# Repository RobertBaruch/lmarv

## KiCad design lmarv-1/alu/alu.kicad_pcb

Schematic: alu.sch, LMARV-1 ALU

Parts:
C1, C2, C3, C4, C5, C14, C15, C16, C24, C25, C26, C27, C28, C29, C30, C31, C32, C33, C34, C35, C36, C37, C38, C39, C40, C41, C42, C43, C44, C45, C46, C47, C48, C49, C50, C51, C52, C57, C58, C59: 100n; C_0603_1608Metric
C100, C101, C102: 1u; CP_Elec_4x4.5
D1, D2: APTD2012LSURCK; D_0805_Wide
P1: dual-pcie-cardedge_split; PCI-EXPRESS
R1, R2, R3, R4: 10k; R_0603_1608Metric
R5, R6: 3k3; R_0603_1608Metric
U1, U14, U16, U26, U27, U37, U40, U41, U42, U43, U44: 74LVC541; TSSOP-20_4.4x6.5mm_P0.65mm
U2: 74LVC04; TSSOP-14_4.4x5mm_P0.65mm
U3: 74LVC32; TSSOP-14_4.4x5mm_P0.65mm
U15: AT28BV64B-20JU; PLCC-32_THT-Socket
U24, U25, U38: 74LVC541_a; TSSOP-20_4.4x6.5mm_P0.65mm
U28, U29, U30, U31, U32, U33, U34, U39, U45, U46, U47, U48, U49, U50, U51, U52: IS61LV256AL; TSOP-I-28_18.4x8mm_Pitch0.55mm
U35: AT28BV256B-20JU; PLCC32
U36: AT28BV64B-20JU; PLCC32
U59: 74LS157; TSSOP-16_4.4x5mm_P0.65mm

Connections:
/BOOT_A[0]: U15.11 (A0), U24.9 (A7), U35.11 (A0), U36.11 (A0); also elsewhere on the board
/BOOT_A[1]: U15.10 (A1), U24.8 (A6), U35.10 (A1), U36.10 (A1); also elsewhere on the board
/BOOT_A[2]: U15.9 (A2), U24.7 (A5), U35.9 (A2), U36.9 (A2); also elsewhere on the board
/BOOT_A[3]: U15.8 (A3), U24.6 (A4), U35.8 (A3), U36.8 (A3); also elsewhere on the board
/BOOT_A[4]: U15.7 (A4), U24.5 (A3), U35.7 (A4), U36.7 (A4); also elsewhere on the board
/BOOT_A[5]: U15.6 (A5), U24.4 (A2), U35.6 (A5), U36.6 (A5); also elsewhere on the board
/BOOT_A[6]: U15.5 (A6), U24.3 (A1), U35.5 (A6), U36.5 (A6); also elsewhere on the board
/BOOT_A[7]: U15.4 (A7), U24.2 (A0), U35.4 (A7), U36.4 (A7); also elsewhere on the board
/BOOT_A[8]: U15.29 (A8), U16.2 (A0), U25.9 (A7), U35.29 (A8), U36.29 (A8); also elsewhere on the board
/BOOT_A[9]: U15.28 (A9), U16.3 (A1), U25.8 (A6), U35.28 (A9), U36.28 (A9); also elsewhere on the board
/BOOT_A[10]: U15.24 (A10), U16.4 (A2), U25.7 (A5), U35.24 (A10), U36.24 (A10); also elsewhere on the board
/BOOT_A[11]: U15.27 (A11), U16.5 (A3), U25.6 (A4), U35.27 (A11), U36.27 (A11); also elsewhere on the board
/BOOT_A[12]: U15.3 (A12), U25.5 (A3), U35.3 (A12), U36.3 (A12), U38.2 (A0), U38.3 (A1), U38.4 (A2), U38.5 (A3), U38.6 (A4), U38.7 (A5), U38.8 (A6), U38.9 (A7); also elsewhere on the board
/BOOT_A[13]: U25.4 (A2), U35.30 (A13); also elsewhere on the board
/BOOT_A[14]: U25.3 (A1), U35.2 (A14); also elsewhere on the board
/BOOT_A[15]: U2.3, U3.12, U16.19 (~G2), U25.2 (A0), U26.19 (~G2), U27.19 (~G2), U38.19 (~G2), U40.19 (~G2), U41.19 (~G2), U42.19 (~G2), U43.19 (~G2), U44.19 (~G2); also elsewhere on the board
/BOOT_CLK: U1.17 (B1); also elsewhere on the board
/BOOT_CLK': P1.194 (BOOT_CLK), U1.3 (A1)
/CLU_D0: U35.13 (I/O0), U37.2 (A0)
/CLU_D1: U35.14 (I/O1), U37.3 (A1)
/CLU_D2: U35.15 (I/O2), U37.4 (A2)
/CLU_D3: U35.18 (I/O3), U37.5 (A3)
/CLU_D4: U35.19 (I/O4), U37.6 (A4)
/CLU_D5: U35.20 (I/O5), U37.7 (A5)
/CLU_D6: U35.21 (I/O6), U37.8 (A6)
/CLU_D7: U35.22 (I/O7), U37.9 (A7)
/SLICE1_CIN: U15.15 (I/O2), U27.8 (A6)
/SLICE1_G: U15.13 (I/O0), U26.2 (A0), U26.4 (A2), U26.6 (A4), U26.8 (A6), U27.2 (A0), U27.4 (A2), U27.6 (A4)
/SLICE1_P: U15.14 (I/O1), U26.3 (A1), U26.5 (A3), U26.7 (A5), U26.9 (A7), U27.3 (A1), U27.5 (A3), U27.7 (A5), U27.9 (A7)
/SLICE2_D[0]: U36.13 (I/O0), U40.2 (A0), U40.6 (A4), U41.2 (A0), U41.6 (A4), U42.2 (A0), U42.6 (A4), U43.2 (A0), U44.2 (A0)
/SLICE2_D[1]: U36.14 (I/O1), U40.3 (A1), U40.7 (A5), U41.3 (A1), U41.7 (A5), U42.3 (A1), U42.7 (A5), U43.3 (A1), U44.3 (A1)
/SLICE2_D[2]: U36.15 (I/O2), U40.4 (A2), U40.8 (A6), U41.4 (A2), U41.8 (A6), U42.4 (A2), U42.8 (A6), U43.4 (A2), U44.4 (A2)
/SLICE2_D[3]: U36.18 (I/O3), U40.5 (A3), U40.9 (A7), U41.5 (A3), U41.9 (A7), U42.5 (A3), U42.9 (A7), U43.5 (A3), U44.5 (A3)
/SLICE2_D[4]: U36.19 (I/O4), U44.6 (A4)
/alu_f[0]: U14.17 (B1), U16.18 (B0), U28.25 (A8), U29.25 (A8), U30.25 (A8), U31.25 (A8), U32.25 (A8), U33.25 (A8), U34.25 (A8), U45.25 (A8), U46.25 (A8), U47.25 (A8), U48.25 (A8), U49.25 (A8), U50.25 (A8), U51.25 (A8), U52.25 (A8)
/alu_f[1]: U14.16 (B2), U16.17 (B1), U28.24 (A9), U29.24 (A9), U30.24 (A9), U31.24 (A9), U32.24 (A9), U33.24 (A9), U34.24 (A9), U45.24 (A9), U46.24 (A9), U47.24 (A9), U48.24 (A9), U49.24 (A9), U50.24 (A9), U51.24 (A9), U52.24 (A9)
/alu_f[2]: U14.15 (B3), U16.16 (B2), U28.21 (A10), U29.21 (A10), U30.21 (A10), U31.21 (A10), U32.21 (A10), U33.21 (A10), U34.21 (A10), U45.21 (A10), U46.21 (A10), U47.21 (A10), U48.21 (A10), U49.21 (A10), U50.21 (A10), U51.21 (A10), U52.21 (A10)
/alu_f[3]: U14.14 (B4), U16.15 (B3), U28.23 (A11), U29.23 (A11), U30.23 (A11), U31.23 (A11), U32.23 (A11), U33.23 (A11), U34.23 (A11), U45.23 (A11), U46.23 (A11), U47.23 (A11), U48.23 (A11), U49.23 (A11), U50.23 (A11), U51.23 (A11), U52.23 (A11)
/cin0': U45.2 (A12), U59.4 (Za)
/cin0_boot: R4.1, U38.11 (B7), U59.3 (I1a)
/cin[0]: U24.11 (B7), U27.12 (B6), U28.13 (I/O2), U39.10 (A0), U59.2 (I0a)
/cin[1]: U37.18 (B0), U38.12 (B6), U39.11 (I/O0), U46.2 (A12)
/cin[2]: U37.17 (B1), U38.13 (B5), U39.12 (I/O1), U47.2 (A12)
/cin[3]: U37.16 (B2), U38.14 (B4), U39.13 (I/O2), U48.2 (A12)
/cin[4]: U37.15 (B3), U38.15 (B3), U39.15 (I/O3), U49.2 (A12)
/cin[5]: U37.14 (B4), U38.16 (B2), U39.16 (I/O4), U50.2 (A12)
/cin[6]: U37.13 (B5), U38.17 (B1), U39.17 (I/O5), U51.2 (A12)
/cin[7]: U37.12 (B6), U38.18 (B0), U39.18 (I/O6), U52.2 (A12)
/cmp[7]: U3.1, U44.14 (B4), U52.16 (I/O4)
/f[0]: P1.188 (f[0]), U14.3 (A1)
/f[1]: P1.190 (f[1]), U14.4 (A2)
/f[2]: P1.191 (f[2]), U14.5 (A3)
/f[3]: P1.192 (f[3]), U14.6 (A4)
/g[0]: U24.12 (B6), U26.18 (B0), U28.11 (I/O0), U39.9 (A1)
/g[1]: U24.14 (B4), U26.16 (B2), U29.11 (I/O0), U39.7 (A3)
/g[2]: U24.16 (B2), U26.14 (B4), U30.11 (I/O0), U39.5 (A5)
/g[3]: U24.18 (B0), U26.12 (B6), U31.11 (I/O0), U39.3 (A7)
/g[4]: U25.12 (B6), U27.18 (B0), U32.11 (I/O0), U39.24 (A9)
/g[5]: U25.14 (B4), U27.16 (B2), U33.11 (I/O0), U39.23 (A11)
/g[6]: U25.16 (B2), U27.14 (B4), U34.11 (I/O0), U39.26 (A13)
/p[0]: U24.13 (B5), U26.17 (B1), U28.12 (I/O1), U39.8 (A2)
/p[1]: U24.15 (B3), U26.15 (B3), U29.12 (I/O1), U39.6 (A4)
/p[2]: U24.17 (B1), U26.13 (B5), U30.12 (I/O1), U39.4 (A6)
/p[3]: U25.11 (B7), U26.11 (B7), U31.12 (I/O1), U39.25 (A8)
/p[4]: U25.13 (B5), U27.17 (B1), U32.12 (I/O1), U39.21 (A10)
/p[5]: U25.15 (B3), U27.15 (B3), U33.12 (I/O1), U39.2 (A12)
/p[6]: U25.17 (B1), U27.13 (B5), U34.12 (I/O1), U39.1 (A14)
/rd[0]: P1.71 (rd[0]); also elsewhere on the board
/rd[1]: P1.70 (rd[1]); also elsewhere on the board
/rd[2]: P1.68 (rd[2]); also elsewhere on the board
/rd[3]: P1.67 (rd[3]); also elsewhere on the board
/rd[4]: P1.65 (rd[4]); also elsewhere on the board
/rd[5]: P1.64 (rd[5]); also elsewhere on the board
/rd[6]: P1.62 (rd[6]); also elsewhere on the board
/rd[7]: P1.61 (rd[7]); also elsewhere on the board
/rd[8]: P1.60 (rd[8]); also elsewhere on the board
/rd[9]: P1.59 (rd[9]); also elsewhere on the board
/rd[10]: P1.57 (rd[10]); also elsewhere on the board
/rd[11]: P1.56 (rd[11]); also elsewhere on the board
/rd[12]: P1.54 (rd[12]); also elsewhere on the board
/rd[13]: P1.53 (rd[13]); also elsewhere on the board
/rd[14]: P1.51 (rd[14]); also elsewhere on the board
/rd[15]: P1.50 (rd[15]); also elsewhere on the board
/rd[16]: P1.22 (rd[16]); also elsewhere on the board
/rd[17]: P1.21 (rd[17]); also elsewhere on the board
/rd[18]: P1.19 (rd[18]); also elsewhere on the board
/rd[19]: P1.18 (rd[19]); also elsewhere on the board
/rd[20]: P1.16 (rd[20]); also elsewhere on the board
/rd[21]: P1.15 (rd[21]); also elsewhere on the board
/rd[22]: P1.13 (rd[22]); also elsewhere on the board
/rd[23]: P1.12 (rd[23]); also elsewhere on the board
/rd[24]: P1.11 (rd[24]); also elsewhere on the board
/rd[25]: P1.10 (rd[25]); also elsewhere on the board
/rd[26]: P1.8 (rd[26]); also elsewhere on the board
/rd[27]: P1.7 (rd[27]); also elsewhere on the board
/rd[28]: P1.5 (rd[28]); also elsewhere on the board
/rd[29]: P1.4 (rd[29]); also elsewhere on the board
/rd[30]: P1.2 (rd[30]); also elsewhere on the board
/rd[31]: P1.1 (rd[31]); also elsewhere on the board
/rdb[0]: U3.2, U40.18 (B0), U45.11 (I/O0)
/rdb[0]': U3.3; also elsewhere on the board
/rdb[1]: U40.17 (B1), U45.12 (I/O1); also elsewhere on the board
/rdb[2]: U40.16 (B2), U45.13 (I/O2); also elsewhere on the board
/rdb[3]: U40.15 (B3), U45.15 (I/O3); also elsewhere on the board
/rdb[4]: U40.14 (B4), U46.11 (I/O0); also elsewhere on the board
/rdb[5]: U40.13 (B5), U46.12 (I/O1); also elsewhere on the board
/rdb[6]: U40.12 (B6), U46.13 (I/O2); also elsewhere on the board
/rdb[7]: U40.11 (B7), U46.15 (I/O3); also elsewhere on the board
/rdb[8]: U41.18 (B0), U47.11 (I/O0); also elsewhere on the board
/rdb[9]: U41.17 (B1), U47.12 (I/O1); also elsewhere on the board
/rdb[10]: U41.16 (B2), U47.13 (I/O2); also elsewhere on the board
/rdb[11]: U41.15 (B3), U47.15 (I/O3); also elsewhere on the board
/rdb[12]: U41.14 (B4), U48.11 (I/O0); also elsewhere on the board
/rdb[13]: U41.13 (B5), U48.12 (I/O1); also elsewhere on the board
/rdb[14]: U41.12 (B6), U48.13 (I/O2); also elsewhere on the board
/rdb[15]: U41.11 (B7), U48.15 (I/O3); also elsewhere on the board
/rdb[16]: U42.18 (B0), U49.11 (I/O0); also elsewhere on the board
/rdb[17]: U42.17 (B1), U49.12 (I/O1); also elsewhere on the board
/rdb[18]: U42.16 (B2), U49.13 (I/O2); also elsewhere on the board
/rdb[19]: U42.15 (B3), U49.15 (I/O3); also elsewhere on the board
/rdb[20]: U42.14 (B4), U50.11 (I/O0); also elsewhere on the board
/rdb[21]: U42.13 (B5), U50.12 (I/O1); also elsewhere on the board
/rdb[22]: U42.12 (B6), U50.13 (I/O2); also elsewhere on the board
/rdb[23]: U42.11 (B7), U50.15 (I/O3); also elsewhere on the board
/rdb[24]: U43.18 (B0), U51.11 (I/O0); also elsewhere on the board
/rdb[25]: U43.17 (B1), U51.12 (I/O1); also elsewhere on the board
/rdb[26]: U43.16 (B2), U51.13 (I/O2); also elsewhere on the board
/rdb[27]: U43.15 (B3), U51.15 (I/O3); also elsewhere on the board
/rdb[28]: U44.18 (B0), U52.11 (I/O0); also elsewhere on the board
/rdb[29]: U44.17 (B1), U52.12 (I/O1); also elsewhere on the board
/rdb[30]: U44.16 (B2), U52.13 (I/O2); also elsewhere on the board
/rdb[31]: U44.15 (B3), U52.15 (I/O3); also elsewhere on the board
/rs1[0]: P1.176 (rs1[0]); also elsewhere on the board
/rs1[1]: P1.174 (rs1[1]); also elsewhere on the board
/rs1[2]: P1.173 (rs1[2]); also elsewhere on the board
/rs1[3]: P1.171 (rs1[3]); also elsewhere on the board
/rs1[4]: P1.170 (rs1[4]); also elsewhere on the board
/rs1[5]: P1.169 (rs1[5]); also elsewhere on the board
/rs1[6]: P1.168 (rs1[6]); also elsewhere on the board
/rs1[7]: P1.166 (rs1[7]); also elsewhere on the board
/rs1[8]: P1.165 (rs1[8]); also elsewhere on the board
/rs1[9]: P1.163 (rs1[9]); also elsewhere on the board
/rs1[10]: P1.162 (rs1[10]); also elsewhere on the board
/rs1[11]: P1.160 (rs1[11]); also elsewhere on the board
/rs1[12]: P1.159 (rs1[12]); also elsewhere on the board
/rs1[13]: P1.158 (rs1[13]); also elsewhere on the board
/rs1[14]: P1.157 (rs1[14]); also elsewhere on the board
/rs1[15]: P1.155 (rs1[15]); also elsewhere on the board
/rs1[16]: P1.120 (rs1[16]); also elsewhere on the board
/rs1[17]: P1.119 (rs1[17]); also elsewhere on the board
/rs1[18]: P1.117 (rs1[18]); also elsewhere on the board
/rs1[19]: P1.116 (rs1[19]); also elsewhere on the board
/rs1[20]: P1.114 (rs1[20]); also elsewhere on the board
/rs1[21]: P1.113 (rs1[21]); also elsewhere on the board
/rs1[22]: P1.111 (rs1[22]); also elsewhere on the board
/rs1[23]: P1.110 (rs1[23]); also elsewhere on the board
/rs1[24]: P1.109 (rs1[24]); also elsewhere on the board
/rs1[25]: P1.108 (rs1[25]); also elsewhere on the board
/rs1[26]: P1.106 (rs1[26]); also elsewhere on the board
/rs1[27]: P1.105 (rs1[27]); also elsewhere on the board
/rs1[28]: P1.103 (rs1[28]); also elsewhere on the board
/rs1[29]: P1.102 (rs1[29]); also elsewhere on the board
/rs1[30]: P1.100 (rs1[30]); also elsewhere on the board
/rs1[31]: P1.99 (rs1[31]); also elsewhere on the board
/rs1b[0]: U28.10 (A0), U45.10 (A0); also elsewhere on the board
/rs1b[1]: U28.9 (A1), U45.9 (A1); also elsewhere on the board
/rs1b[2]: U28.8 (A2), U45.8 (A2); also elsewhere on the board
/rs1b[3]: U28.7 (A3), U45.7 (A3); also elsewhere on the board
/rs1b[4]: U29.10 (A0), U46.10 (A0); also elsewhere on the board
/rs1b[5]: U29.9 (A1), U46.9 (A1); also elsewhere on the board
/rs1b[6]: U29.8 (A2), U46.8 (A2); also elsewhere on the board
/rs1b[7]: U29.7 (A3), U46.7 (A3); also elsewhere on the board
/rs1b[8]: U30.10 (A0), U47.10 (A0); also elsewhere on the board
/rs1b[9]: U30.9 (A1), U47.9 (A1); also elsewhere on the board
/rs1b[10]: U30.8 (A2), U47.8 (A2); also elsewhere on the board
/rs1b[11]: U30.7 (A3), U47.7 (A3); also elsewhere on the board
/rs1b[12]: U31.10 (A0), U48.10 (A0); also elsewhere on the board
/rs1b[13]: U31.9 (A1), U48.9 (A1); also elsewhere on the board
/rs1b[14]: U31.8 (A2), U48.8 (A2); also elsewhere on the board
/rs1b[15]: U31.7 (A3), U48.7 (A3); also elsewhere on the board
/rs1b[16]: U32.10 (A0), U49.10 (A0); also elsewhere on the board
/rs1b[17]: U32.9 (A1), U49.9 (A1); also elsewhere on the board
/rs1b[18]: U32.8 (A2), U49.8 (A2); also elsewhere on the board
/rs1b[19]: U32.7 (A3), U49.7 (A3); also elsewhere on the board
/rs1b[20]: U33.10 (A0), U50.10 (A0); also elsewhere on the board
/rs1b[21]: U33.9 (A1), U50.9 (A1); also elsewhere on the board
/rs1b[22]: U33.8 (A2), U50.8 (A2); also elsewhere on the board
/rs1b[23]: U33.7 (A3), U50.7 (A3); also elsewhere on the board
/rs1b[24]: U34.10 (A0), U51.10 (A0); also elsewhere on the board
/rs1b[25]: U34.9 (A1), U51.9 (A1); also elsewhere on the board
/rs1b[26]: U34.8 (A2), U51.8 (A2); also elsewhere on the board
/rs1b[27]: U34.7 (A3), U51.7 (A3); also elsewhere on the board
/rs1b[28]: U52.10 (A0); also elsewhere on the board
/rs1b[29]: U52.9 (A1); also elsewhere on the board
/rs1b[30]: U52.8 (A2); also elsewhere on the board
/rs1b[31]: U52.7 (A3); also elsewhere on the board
/rs2[0]: P1.93 (rs2[0]); also elsewhere on the board
/rs2[1]: P1.92 (rs2[1]); also elsewhere on the board
/rs2[2]: P1.90 (rs2[2]); also elsewhere on the board
/rs2[3]: P1.89 (rs2[3]); also elsewhere on the board
/rs2[4]: P1.87 (rs2[4]); also elsewhere on the board
/rs2[5]: P1.86 (rs2[5]); also elsewhere on the board
/rs2[6]: P1.84 (rs2[6]); also elsewhere on the board
/rs2[7]: P1.83 (rs2[7]); also elsewhere on the board
/rs2[8]: P1.82 (rs2[8]); also elsewhere on the board
/rs2[9]: P1.81 (rs2[9]); also elsewhere on the board
/rs2[10]: P1.79 (rs2[10]); also elsewhere on the board
/rs2[11]: P1.78 (rs2[11]); also elsewhere on the board
/rs2[12]: P1.76 (rs2[12]); also elsewhere on the board
/rs2[13]: P1.75 (rs2[13]); also elsewhere on the board
/rs2[14]: P1.73 (rs2[14]); also elsewhere on the board
/rs2[15]: P1.72 (rs2[15]); also elsewhere on the board
/rs2[16]: P1.44 (rs2[16]); also elsewhere on the board
/rs2[17]: P1.43 (rs2[17]); also elsewhere on the board
/rs2[18]: P1.41 (rs2[18]); also elsewhere on the board
/rs2[19]: P1.40 (rs2[19]); also elsewhere on the board
/rs2[20]: P1.38 (rs2[20]); also elsewhere on the board
/rs2[21]: P1.37 (rs2[21]); also elsewhere on the board
/rs2[22]: P1.35 (rs2[22]); also elsewhere on the board
/rs2[23]: P1.34 (rs2[23]); also elsewhere on the board
/rs2[24]: P1.33 (rs2[24]); also elsewhere on the board
/rs2[25]: P1.32 (rs2[25]); also elsewhere on the board
/rs2[26]: P1.30 (rs2[26]); also elsewhere on the board
/rs2[27]: P1.29 (rs2[27]); also elsewhere on the board
/rs2[28]: P1.27 (rs2[28]); also elsewhere on the board
/rs2[29]: P1.26 (rs2[29]); also elsewhere on the board
/rs2[30]: P1.24 (rs2[30]); also elsewhere on the board
/rs2[31]: P1.23 (rs2[31]); also elsewhere on the board
/rs2b[0]: U28.6 (A4), U45.6 (A4); also elsewhere on the board
/rs2b[1]: U28.5 (A5), U45.5 (A5); also elsewhere on the board
/rs2b[2]: U28.4 (A6), U45.4 (A6); also elsewhere on the board
/rs2b[3]: U28.3 (A7), U45.3 (A7); also elsewhere on the board
/rs2b[4]: U29.6 (A4), U46.6 (A4); also elsewhere on the board
/rs2b[5]: U29.5 (A5), U46.5 (A5); also elsewhere on the board
/rs2b[6]: U29.4 (A6), U46.4 (A6); also elsewhere on the board
/rs2b[7]: U29.3 (A7), U46.3 (A7); also elsewhere on the board
/rs2b[8]: U30.6 (A4), U47.6 (A4); also elsewhere on the board
/rs2b[9]: U30.5 (A5), U47.5 (A5); also elsewhere on the board
/rs2b[10]: U30.4 (A6), U47.4 (A6); also elsewhere on the board
/rs2b[11]: U30.3 (A7), U47.3 (A7); also elsewhere on the board
/rs2b[12]: U31.6 (A4), U48.6 (A4); also elsewhere on the board
/rs2b[13]: U31.5 (A5), U48.5 (A5); also elsewhere on the board
/rs2b[14]: U31.4 (A6), U48.4 (A6); also elsewhere on the board
/rs2b[15]: U31.3 (A7), U48.3 (A7); also elsewhere on the board
/rs2b[16]: U32.6 (A4), U49.6 (A4); also elsewhere on the board
/rs2b[17]: U32.5 (A5), U49.5 (A5); also elsewhere on the board
/rs2b[18]: U32.4 (A6), U49.4 (A6); also elsewhere on the board
/rs2b[19]: U32.3 (A7), U49.3 (A7); also elsewhere on the board
/rs2b[20]: U33.6 (A4), U50.6 (A4); also elsewhere on the board
/rs2b[21]: U33.5 (A5), U50.5 (A5); also elsewhere on the board
/rs2b[22]: U33.4 (A6), U50.4 (A6); also elsewhere on the board
/rs2b[23]: U33.3 (A7), U50.3 (A7); also elsewhere on the board
/rs2b[24]: U34.6 (A4), U51.6 (A4); also elsewhere on the board
/rs2b[25]: U34.5 (A5), U51.5 (A5); also elsewhere on the board
/rs2b[26]: U34.4 (A6), U51.4 (A6); also elsewhere on the board
/rs2b[27]: U34.3 (A7), U51.3 (A7); also elsewhere on the board
/rs2b[28]: U52.6 (A4); also elsewhere on the board
/rs2b[29]: U52.5 (A5); also elsewhere on the board
/rs2b[30]: U52.4 (A6); also elsewhere on the board
/rs2b[31]: U52.3 (A7); also elsewhere on the board
/~BOOT_ALU_EN: R1.2, U1.18 (B0), U2.1, U3.5, U16.1 (~G1), U24.1 (~G1), U25.1 (~G1), U26.1 (~G1), U27.1 (~G1), U37.1 (~G1), U38.1 (~G1), U40.1 (~G1), U41.1 (~G1), U42.1 (~G1), U43.1 (~G1), U44.1 (~G1); also elsewhere on the board
/~BOOT_ALU_EN': P1.193 (~BOOT_ALU_EN), U1.2 (A0)
/~BOOT_ALU_WR: U3.6, U3.10, U3.13
/~BOOT_A[15]: U2.4, U3.9, U24.19 (~G2), U25.19 (~G2), U37.19 (~G2)
/~BOOT_PH0_WR: U3.11, U28.27 (~WE), U29.27 (~WE), U30.27 (~WE), U31.27 (~WE), U32.27 (~WE), U33.27 (~WE), U34.27 (~WE), U45.27 (~WE), U46.27 (~WE), U47.27 (~WE), U48.27 (~WE), U49.27 (~WE), U50.27 (~WE), U51.27 (~WE), U52.27 (~WE)
/~BOOT_PH1_WR: U3.8, U39.27 (~WE)
/~BOOT_RST': P1.195 (~BOOT_RST), U1.4 (A2)
/~BOOT_WR: U1.15 (B3), U3.4
/~BOOT_WR': P1.196 (~BOOT_WR), U1.5 (A3)
/~alu_oe: R3.2, U14.18 (B0); also elsewhere on the board
/~alu_oe': P1.187 (/alu_oe), U14.2 (A0), U14.7 (A5)
/~alu_oe_led: D2.1 (K), U14.13 (B5)
unnamed: D1.2 (A), R5.2
unnamed: D2.2 (A), R6.2

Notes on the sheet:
BOOT PROCEDURE: 1. DISABLE ALL CONTROL LINES (INCLUDES ~alu_oe~) 2. SET ~BOOT_ALU_EN~ LOW 3. STROBE ~BOOT_RST~ LOW 4. STROBE BOOT_CLK HIGH 5. STROBE ~BOOT_WR~ LOW 6. REPEAT 4 & 5 64K TIMES 7. SET ~BOOT_ALU_EN~ HIGH
BUFFERS ENABLED DURING BOOT PHASE 0
BUFFERS ENABLED DURING BOOT PHASE 1
BUFFER ENABLED DURING BOOT PHASE 1
CARRY LOOKAHEAD UNIT
ALU BOOT COUNTER
PROPAGATE/GENERATE BIT SLICE
ARITHMETIC BIT SLICE
BUFFER ENABLED DURING BOOT PHASE 0
CARRY LOOKAHEAD UNIT ROM
PROPAGATE/GENERATE ROM
ARITHMETIC BIT SLICE ROM
A15&~ALU_BOOT_WR~

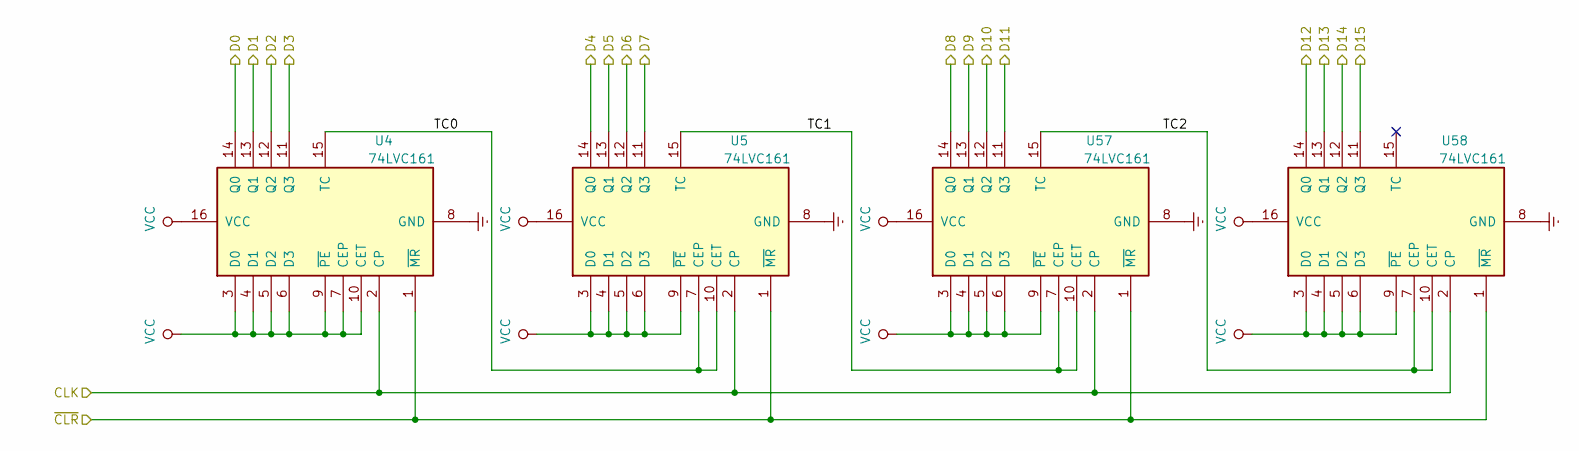
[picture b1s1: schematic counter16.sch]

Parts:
U4, U5, U57, U58: 74LVC161; TSSOP-16_4.4x5mm_P0.65mm

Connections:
/BOOT_A[0]: U4.14 (Q0); also elsewhere on the board
/BOOT_A[1]: U4.13 (Q1); also elsewhere on the board
/BOOT_A[2]: U4.12 (Q2); also elsewhere on the board
/BOOT_A[3]: U4.11 (Q3); also elsewhere on the board
/BOOT_A[4]: U5.14 (B4); also elsewhere on the board
/BOOT_A[5]: U5.13 (B5); also elsewhere on the board
/BOOT_A[6]: U5.12 (B6); also elsewhere on the board
/BOOT_A[7]: U5.11 (B7); also elsewhere on the board
/BOOT_A[8]: U57.14 (Q0); also elsewhere on the board
/BOOT_A[9]: U57.13 (Q1); also elsewhere on the board
/BOOT_A[10]: U57.12 (Q2); also elsewhere on the board
/BOOT_A[11]: U57.11 (Q3); also elsewhere on the board
/BOOT_A[12]: U58.14 (Q0); also elsewhere on the board
/BOOT_A[13]: U58.13 (Q1); also elsewhere on the board
/BOOT_A[14]: U58.12 (Q2); also elsewhere on the board
/BOOT_A[15]: U58.11 (Q3); also elsewhere on the board
/BOOT_CLK: U4.2 (CP), U5.2 (A0), U57.2 (CP), U58.2 (CP); also elsewhere on the board
/counter16/TC1: U5.15 (B3), U57.7 (CEP), U57.10 (CET)
/counter16/TC2: U57.15 (TC), U58.7 (CEP), U58.10 (CET)

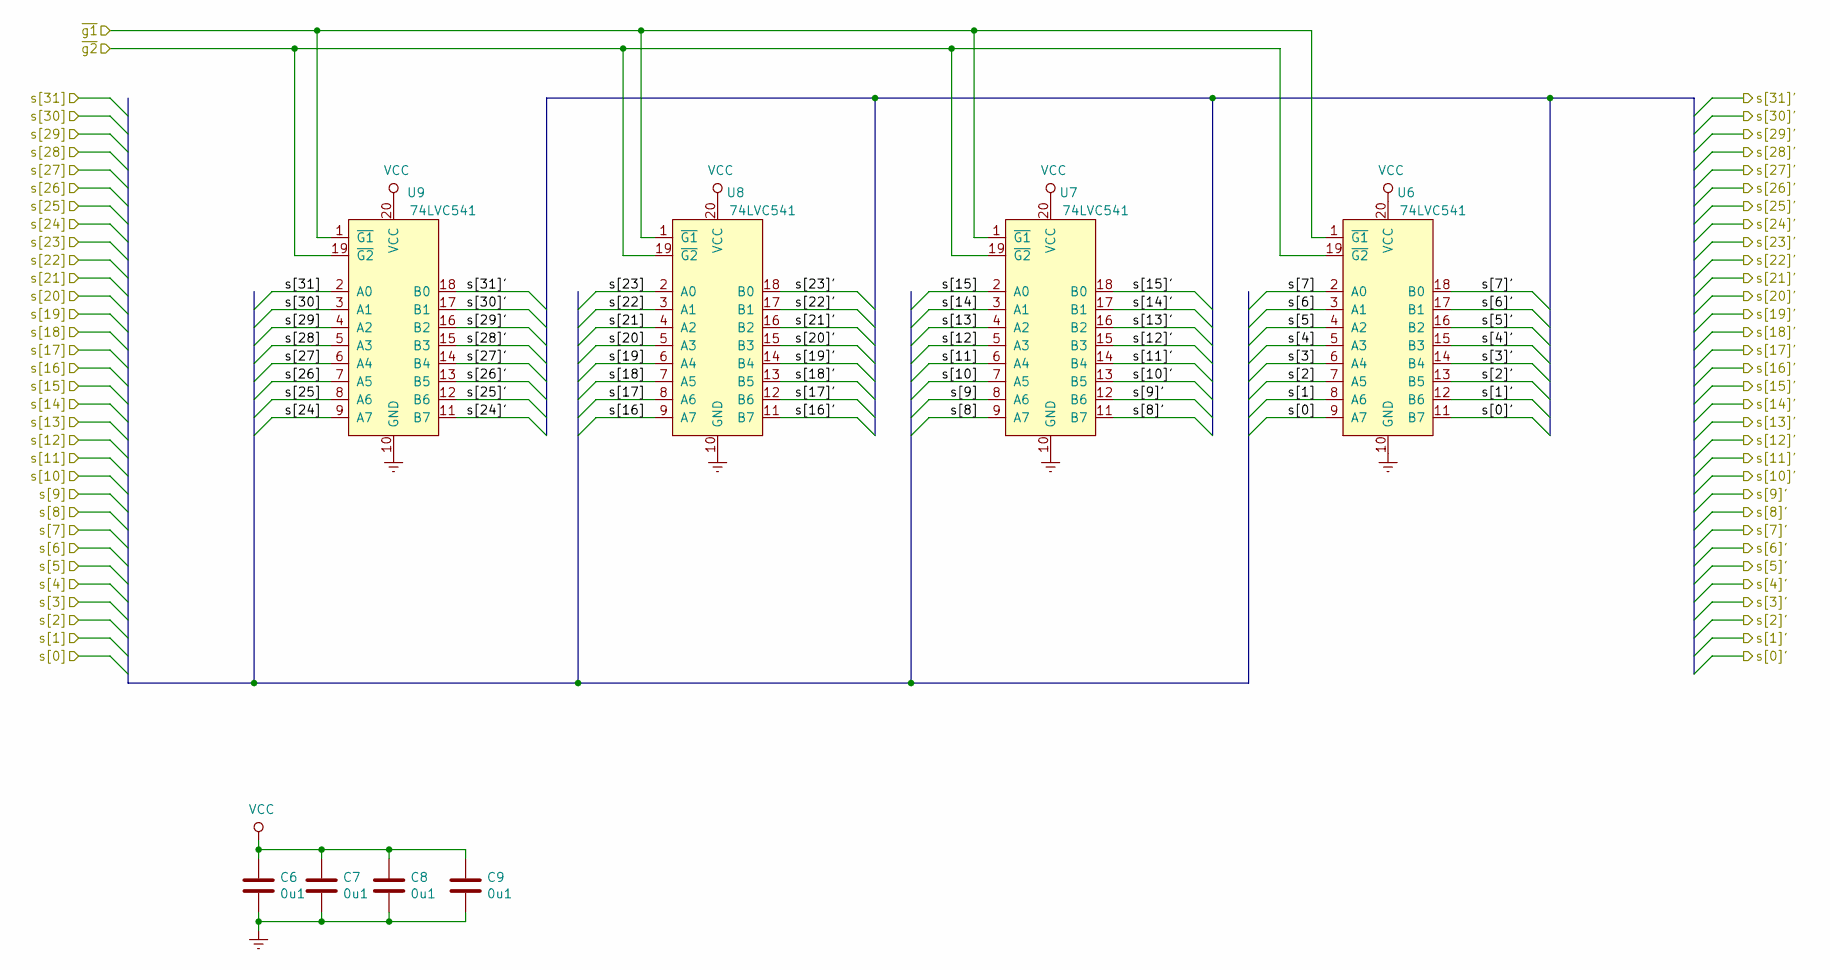
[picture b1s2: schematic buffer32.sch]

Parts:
C13, C14, C15, C16: 0u1; C_0603_1608Metric
U5, U6, U7, U8: 74LVC541; TSSOP-20_4.4x6.5mm_P0.65mm

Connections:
/BOOT_A[4]: U5.14 (B4); also elsewhere on the board
/BOOT_A[5]: U5.13 (B5); also elsewhere on the board
/BOOT_A[6]: U5.12 (B6); also elsewhere on the board
/BOOT_A[7]: U5.11 (B7); also elsewhere on the board
/BOOT_CLK: U5.2 (A0); also elsewhere on the board
/counter16/TC1: U5.15 (B3); also elsewhere on the board
/rs1[0]: U6.9 (A7); also elsewhere on the board
/rs1[1]: U6.8 (A6); also elsewhere on the board
/rs1[2]: U6.7 (A5); also elsewhere on the board
/rs1[3]: U6.6 (A4); also elsewhere on the board
/rs1[4]: U6.5 (A3); also elsewhere on the board
/rs1[5]: U6.4 (A2); also elsewhere on the board
/rs1[6]: U6.3 (A1); also elsewhere on the board
/rs1[7]: U6.2 (A0); also elsewhere on the board
/rs1[8]: U7.9 (A7); also elsewhere on the board
/rs1[9]: U7.8 (A6); also elsewhere on the board
/rs1[10]: U7.7 (A5); also elsewhere on the board
/rs1[11]: U7.6 (A4); also elsewhere on the board
/rs1[12]: U7.5 (A3); also elsewhere on the board
/rs1[13]: U7.4 (A2); also elsewhere on the board
/rs1[14]: U7.3 (A1); also elsewhere on the board
/rs1[15]: U7.2 (A0); also elsewhere on the board
/rs1[16]: U8.9 (A7); also elsewhere on the board
/rs1[17]: U8.8 (A6); also elsewhere on the board
/rs1[18]: U8.7 (A5); also elsewhere on the board
/rs1[19]: U8.6 (A4); also elsewhere on the board
/rs1[20]: U8.5 (A3); also elsewhere on the board
/rs1[21]: U8.4 (A2); also elsewhere on the board
/rs1[22]: U8.3 (A1); also elsewhere on the board
/rs1[23]: U8.2 (A0); also elsewhere on the board
/rs1b[0]: U6.11 (B7); also elsewhere on the board
/rs1b[1]: U6.12 (B6); also elsewhere on the board
/rs1b[2]: U6.13 (B5); also elsewhere on the board
/rs1b[3]: U6.14 (B4); also elsewhere on the board
/rs1b[4]: U6.15 (B3); also elsewhere on the board
/rs1b[5]: U6.16 (B2); also elsewhere on the board
/rs1b[6]: U6.17 (B1); also elsewhere on the board
/rs1b[7]: U6.18 (B0); also elsewhere on the board
/rs1b[8]: U7.11 (B7); also elsewhere on the board
/rs1b[9]: U7.12 (B6); also elsewhere on the board
/rs1b[10]: U7.13 (B5); also elsewhere on the board
/rs1b[11]: U7.14 (B4); also elsewhere on the board
/rs1b[12]: U7.15 (B3); also elsewhere on the board
/rs1b[13]: U7.16 (B2); also elsewhere on the board
/rs1b[14]: U7.17 (B1); also elsewhere on the board
/rs1b[15]: U7.18 (B0); also elsewhere on the board
/rs1b[16]: U8.11 (B7); also elsewhere on the board
/rs1b[17]: U8.12 (B6); also elsewhere on the board
/rs1b[18]: U8.13 (B5); also elsewhere on the board
/rs1b[19]: U8.14 (B4); also elsewhere on the board
/rs1b[20]: U8.15 (B3); also elsewhere on the board
/rs1b[21]: U8.16 (B2); also elsewhere on the board
/rs1b[22]: U8.17 (B1); also elsewhere on the board
/rs1b[23]: U8.18 (B0); also elsewhere on the board

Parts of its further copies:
C6, C7, C8, C9, C10, C11, C12, C17, C18, C19, C20, C21, C22, C23, C53, C54, C55, C56, C60: 0u1; C_0603_1608Metric
U9, U10, U11, U12, U13, U17, U18, U19, U20, U21, U22, U23, U60: 74LVC541; TSSOP-20_4.4x6.5mm_P0.65mm

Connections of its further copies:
/BOOT_A[0]: U17.2 (A0), U18.2 (A0), U19.2 (A0), U20.2 (A0), U21.2 (A0), U22.2 (A0), U23.2 (A0), U60.2 (A0); also elsewhere on the board
/BOOT_A[1]: U17.3 (A1), U18.3 (A1), U19.3 (A1), U20.3 (A1), U21.3 (A1), U22.3 (A1), U23.3 (A1), U60.3 (A1); also elsewhere on the board
/BOOT_A[2]: U17.4 (A2), U18.4 (A2), U19.4 (A2), U20.4 (A2), U21.4 (A2), U22.4 (A2), U23.4 (A2), U60.4 (A2); also elsewhere on the board
/BOOT_A[3]: U17.5 (A3), U18.5 (A3), U19.5 (A3), U20.5 (A3), U21.5 (A3), U22.5 (A3), U23.5 (A3), U60.5 (A3); also elsewhere on the board
/BOOT_A[4]: U17.6 (A4), U18.6 (A4), U19.6 (A4), U20.6 (A4), U21.6 (A4), U22.6 (A4), U23.6 (A4), U60.6 (A4); also elsewhere on the board
/BOOT_A[5]: U17.7 (A5), U18.7 (A5), U19.7 (A5), U20.7 (A5), U21.7 (A5), U22.7 (A5), U23.7 (A5), U60.7 (A5); also elsewhere on the board
/BOOT_A[6]: U17.8 (A6), U18.8 (A6), U19.8 (A6), U20.8 (A6), U21.8 (A6), U22.8 (A6), U23.8 (A6), U60.8 (A6); also elsewhere on the board
/BOOT_A[7]: U17.9 (A7), U18.9 (A7), U19.9 (A7), U20.9 (A7), U21.9 (A7), U22.9 (A7), U23.9 (A7), U60.9 (A7); also elsewhere on the board
/BOOT_A[15]: U17.19 (~G2), U18.19 (~G2), U19.19 (~G2), U20.19 (~G2), U21.1 (~G1), U22.1 (~G1), U23.1 (~G1), U60.1 (~G1); also elsewhere on the board
/rs1[24]: U9.9 (A7); also elsewhere on the board
/rs1[25]: U9.8 (A6); also elsewhere on the board
/rs1[26]: U9.7 (A5); also elsewhere on the board
/rs1[27]: U9.6 (A4); also elsewhere on the board
/rs1[28]: U9.5 (A3); also elsewhere on the board
/rs1[29]: U9.4 (A2); also elsewhere on the board
/rs1[30]: U9.3 (A1); also elsewhere on the board
/rs1[31]: U9.2 (A0); also elsewhere on the board
/rs1b[0]: U17.18 (B0); also elsewhere on the board
/rs1b[1]: U17.17 (B1); also elsewhere on the board
/rs1b[2]: U17.16 (B2); also elsewhere on the board
/rs1b[3]: U17.15 (B3); also elsewhere on the board
/rs1b[4]: U18.18 (B0); also elsewhere on the board
/rs1b[5]: U18.17 (B1); also elsewhere on the board
/rs1b[6]: U18.16 (B2); also elsewhere on the board
/rs1b[7]: U18.15 (B3); also elsewhere on the board
/rs1b[8]: U19.18 (B0); also elsewhere on the board
/rs1b[9]: U19.17 (B1); also elsewhere on the board
/rs1b[10]: U19.16 (B2); also elsewhere on the board
/rs1b[11]: U19.15 (B3); also elsewhere on the board
/rs1b[12]: U20.18 (B0); also elsewhere on the board
/rs1b[13]: U20.17 (B1); also elsewhere on the board
/rs1b[14]: U20.16 (B2); also elsewhere on the board
/rs1b[15]: U20.15 (B3); also elsewhere on the board
/rs1b[16]: U21.18 (B0); also elsewhere on the board
/rs1b[17]: U21.17 (B1); also elsewhere on the board
/rs1b[18]: U21.16 (B2); also elsewhere on the board
/rs1b[19]: U21.15 (B3); also elsewhere on the board
/rs1b[20]: U22.18 (B0); also elsewhere on the board
/rs1b[21]: U22.17 (B1); also elsewhere on the board
/rs1b[22]: U22.16 (B2); also elsewhere on the board
/rs1b[23]: U22.15 (B3); also elsewhere on the board
/rs1b[24]: U9.11 (B7), U23.18 (B0); also elsewhere on the board
/rs1b[25]: U9.12 (B6), U23.17 (B1); also elsewhere on the board
/rs1b[26]: U9.13 (B5), U23.16 (B2); also elsewhere on the board
/rs1b[27]: U9.14 (B4), U23.15 (B3); also elsewhere on the board
/rs1b[28]: U9.15 (B3), U60.18 (B0); also elsewhere on the board
/rs1b[29]: U9.16 (B2), U60.17 (B1); also elsewhere on the board
/rs1b[30]: U9.17 (B1), U60.16 (B2); also elsewhere on the board
/rs1b[31]: U9.18 (B0), U60.15 (B3); also elsewhere on the board
/rs2[0]: U10.9 (A7); also elsewhere on the board
/rs2[1]: U10.8 (A6); also elsewhere on the board
/rs2[2]: U10.7 (A5); also elsewhere on the board
/rs2[3]: U10.6 (A4); also elsewhere on the board
/rs2[4]: U10.5 (A3); also elsewhere on the board
/rs2[5]: U10.4 (A2); also elsewhere on the board
/rs2[6]: U10.3 (A1); also elsewhere on the board
/rs2[7]: U10.2 (A0); also elsewhere on the board
/rs2[8]: U11.9 (A7); also elsewhere on the board
/rs2[9]: U11.8 (A6); also elsewhere on the board
/rs2[10]: U11.7 (A5); also elsewhere on the board
/rs2[11]: U11.6 (A4); also elsewhere on the board
/rs2[12]: U11.5 (A3); also elsewhere on the board
/rs2[13]: U11.4 (A2); also elsewhere on the board
/rs2[14]: U11.3 (A1); also elsewhere on the board
/rs2[15]: U11.2 (A0); also elsewhere on the board
/rs2[16]: U12.9 (A7); also elsewhere on the board
/rs2[17]: U12.8 (A6); also elsewhere on the board
/rs2[18]: U12.7 (A5); also elsewhere on the board
/rs2[19]: U12.6 (A4); also elsewhere on the board
/rs2[20]: U12.5 (A3); also elsewhere on the board
/rs2[21]: U12.4 (A2); also elsewhere on the board
/rs2[22]: U12.3 (A1); also elsewhere on the board
/rs2[23]: U12.2 (A0); also elsewhere on the board
/rs2[24]: U13.9 (A7); also elsewhere on the board
/rs2[25]: U13.8 (A6); also elsewhere on the board
/rs2[26]: U13.7 (A5); also elsewhere on the board
/rs2[27]: U13.6 (A4); also elsewhere on the board
/rs2[28]: U13.5 (A3); also elsewhere on the board
/rs2[29]: U13.4 (A2); also elsewhere on the board
/rs2[30]: U13.3 (A1); also elsewhere on the board
/rs2[31]: U13.2 (A0); also elsewhere on the board
/rs2b[0]: U10.11 (B7), U17.14 (B4); also elsewhere on the board
/rs2b[1]: U10.12 (B6), U17.13 (B5); also elsewhere on the board
/rs2b[2]: U10.13 (B5), U17.12 (B6); also elsewhere on the board
/rs2b[3]: U10.14 (B4), U17.11 (B7); also elsewhere on the board
/rs2b[4]: U10.15 (B3), U18.14 (B4); also elsewhere on the board
/rs2b[5]: U10.16 (B2), U18.13 (B5); also elsewhere on the board
/rs2b[6]: U10.17 (B1), U18.12 (B6); also elsewhere on the board
/rs2b[7]: U10.18 (B0), U18.11 (B7); also elsewhere on the board
/rs2b[8]: U11.11 (B7), U19.14 (B4); also elsewhere on the board
/rs2b[9]: U11.12 (B6), U19.13 (B5); also elsewhere on the board
/rs2b[10]: U11.13 (B5), U19.12 (B6); also elsewhere on the board
/rs2b[11]: U11.14 (B4), U19.11 (B7); also elsewhere on the board
/rs2b[12]: U11.15 (B3), U20.14 (B4); also elsewhere on the board
/rs2b[13]: U11.16 (B2), U20.13 (B5); also elsewhere on the board
/rs2b[14]: U11.17 (B1), U20.12 (B6); also elsewhere on the board
/rs2b[15]: U11.18 (B0), U20.11 (B7); also elsewhere on the board
/rs2b[16]: U12.11 (B7), U21.14 (B4); also elsewhere on the board
/rs2b[17]: U12.12 (B6), U21.13 (B5); also elsewhere on the board
/rs2b[18]: U12.13 (B5), U21.12 (B6); also elsewhere on the board
/rs2b[19]: U12.14 (B4), U21.11 (B7); also elsewhere on the board
/rs2b[20]: U12.15 (B3), U22.14 (B4); also elsewhere on the board
/rs2b[21]: U12.16 (B2), U22.13 (B5); also elsewhere on the board
/rs2b[22]: U12.17 (B1), U22.12 (B6); also elsewhere on the board
/rs2b[23]: U12.18 (B0), U22.11 (B7); also elsewhere on the board
/rs2b[24]: U13.11 (B7), U23.14 (B4); also elsewhere on the board
/rs2b[25]: U13.12 (B6), U23.13 (B5); also elsewhere on the board
/rs2b[26]: U13.13 (B5), U23.12 (B6); also elsewhere on the board
/rs2b[27]: U13.14 (B4), U23.11 (B7); also elsewhere on the board
/rs2b[28]: U13.15 (B3), U60.14 (B4); also elsewhere on the board
/rs2b[29]: U13.16 (B2), U60.13 (B5); also elsewhere on the board
/rs2b[30]: U13.17 (B1), U60.12 (B6); also elsewhere on the board
/rs2b[31]: U13.18 (B0), U60.11 (B7); also elsewhere on the board
/~BOOT_ALU_EN: U17.1 (~G1), U18.1 (~G1), U19.1 (~G1), U20.1 (~G1), U21.19 (~G2), U22.19 (~G2), U23.19 (~G2), U60.19 (~G2); also elsewhere on the board
